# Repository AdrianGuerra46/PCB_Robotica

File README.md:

# PCB Robótica Industrial

Este proyecto fue realizado para compactar y profesionalizar el apartado electrónico del proyecto final de la asignatura Robótica industrial (materia de pregrado de ingeniería mecatrónica en la Universidad EIA) el cual fue construir un Robot Scara. 

Esta PCB debia generar conexión entre los siguientes componentes: 

- Raspberry Pi Pico
- Driver Dual motor TB6612FNG
- Servo Motor "Micro Servo 9g"
- Dos motores DC 12V - 200RPM con Encoder
- 4 Finales de Carrera

La PCB fue diseñada y exportada desde el software Kicad7.

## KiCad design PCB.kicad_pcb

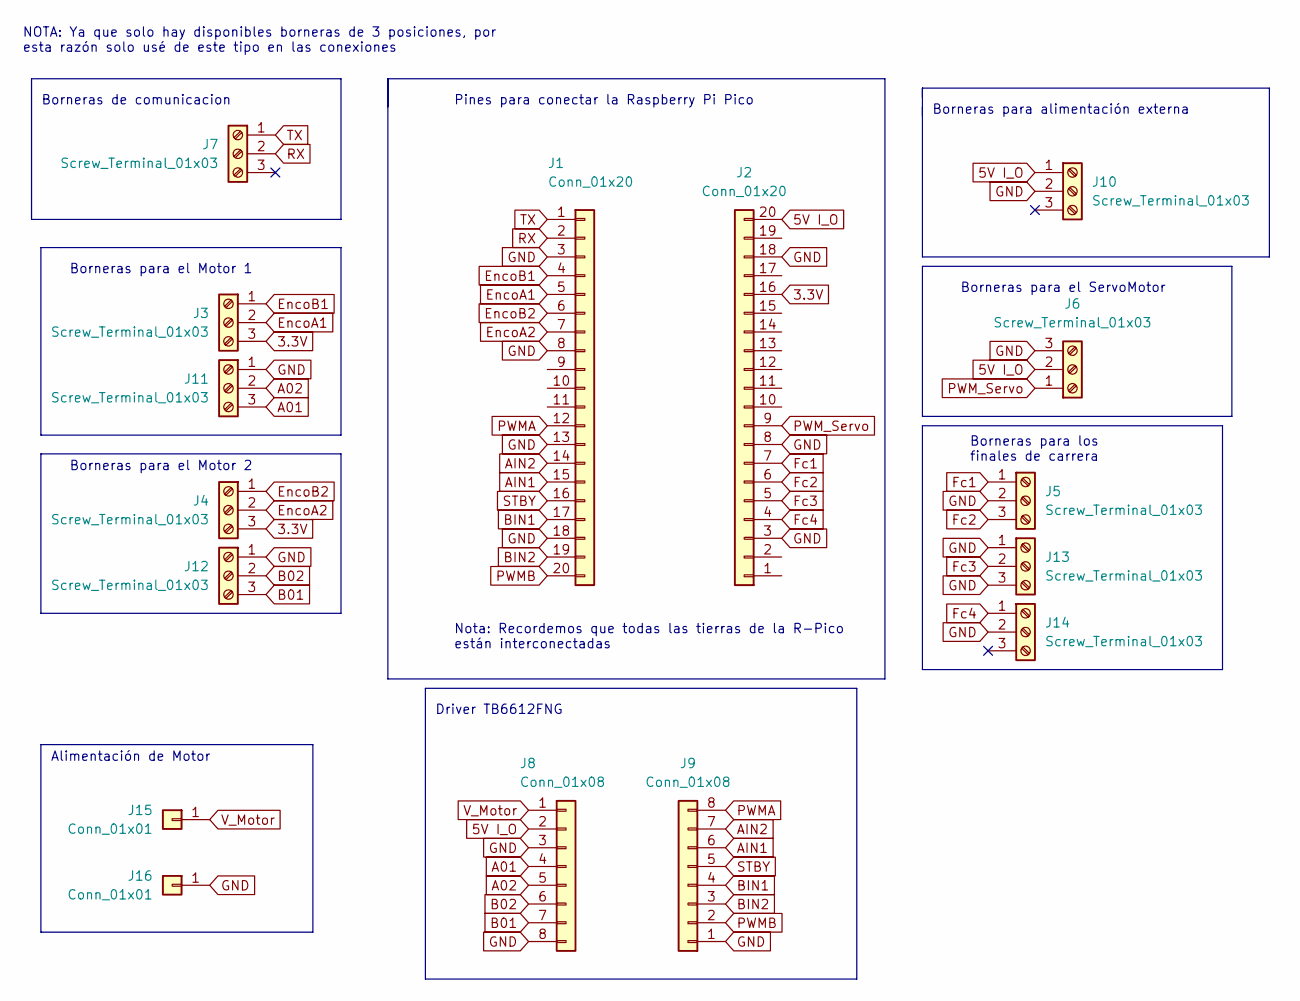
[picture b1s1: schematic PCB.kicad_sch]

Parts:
J1, J2: Conn_01x20; PinSocket_1x20_P2.54mm_Vertical
J3, J4, J5, J6, J7, J10, J11, J12, J13, J14: Screw_Terminal_01x03; PhoenixContact_MSTBVA_2,5_3-G_1x03_P5.00mm_Vertical
J8, J9: Conn_01x08; PinSocket_1x08_P2.54mm_Vertical
J15, J16: Conn_01x01; PinHeader_1x01_P2.54mm_Vertical

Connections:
3.3V: J2.16, J3.3, J4.3
5V I_O: J2.20, J6.2, J8.2, J10.1
A01: J8.4, J11.3
A02: J8.5, J11.2
AIN1: J1.15, J9.6
AIN2: J1.14, J9.7
B01: J8.7, J12.3
B02: J8.6, J12.2
BIN1: J1.17, J9.4
BIN2: J1.19, J9.3
EncoA1: J1.5, J3.2
EncoA2: J1.7, J4.2
EncoB1: J1.4, J3.1
EncoB2: J1.6, J4.1
Fc1: J2.7, J5.1
Fc2: J2.6, J5.3
Fc3: J2.5, J13.2
Fc4: J2.4, J14.1
GND: J1.3, J1.8, J1.13, J1.18, J2.3, J2.8, J2.18, J5.2, J6.3, J8.3, J8.8, J9.1, J10.2, J11.1, J12.1, J13.1, J13.3, J14.2, J16.1
PWMA: J1.12, J9.8
PWMB: J1.20, J9.2
PWM_Servo: J2.9, J6.1
RX: J1.2, J7.2
STBY: J1.16, J9.5
TX: J1.1, J7.1
V_Motor: J8.1, J15.1

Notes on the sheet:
Nota: Recordemos que todas las tierras de la R-Pico están interconectadas
Alimentación de Motor
Borneras para el ServoMotor
Borneras de comunicacion
Borneras para el Motor 1
Driver TB6612FNG
Pines para conectar la Raspberry Pi Pico
Borneras para el Motor 2
Borneras para los finales de carrera
Borneras para alimentación externa
NOTA: Ya que solo hay disponibles borneras de 3 posiciones, por esta razón solo usé de este tipo en las conexiones

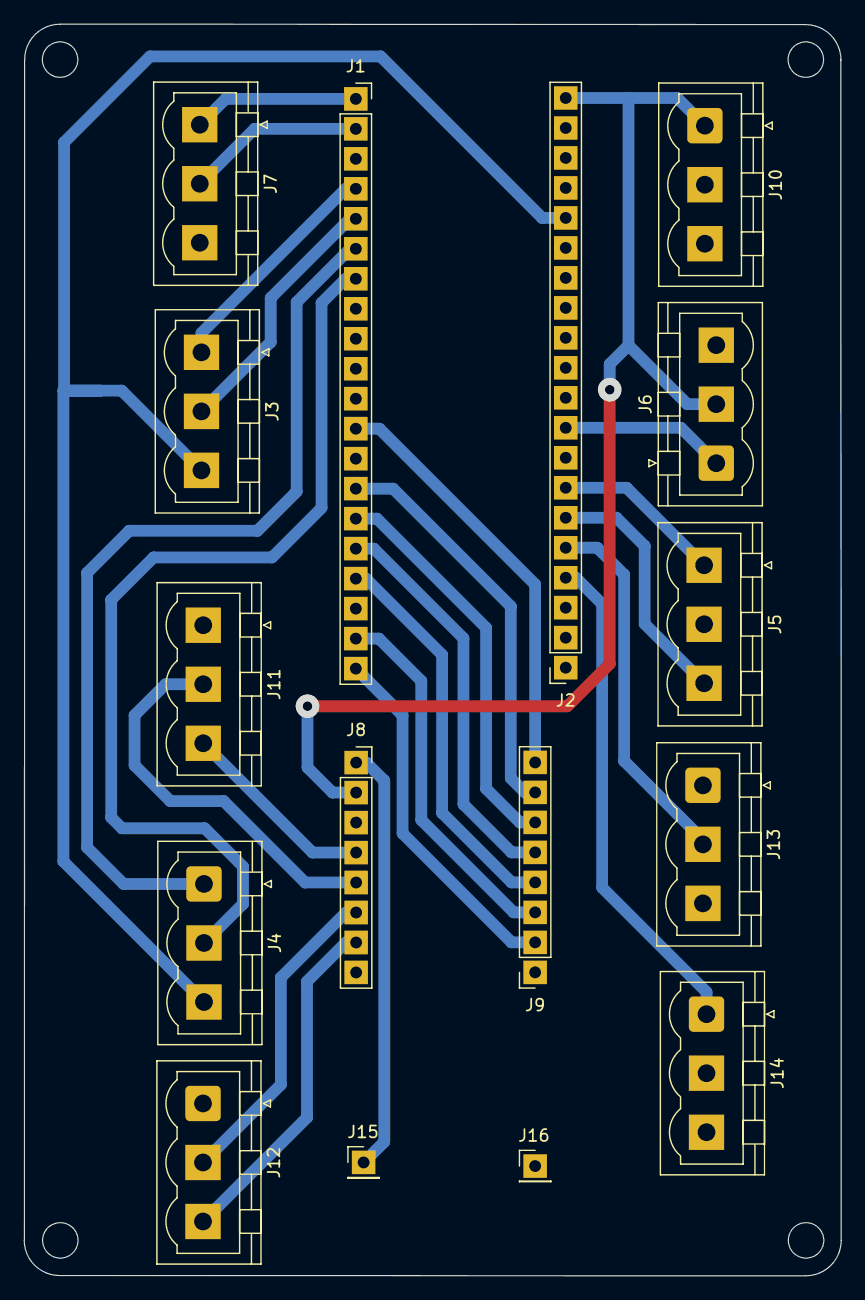
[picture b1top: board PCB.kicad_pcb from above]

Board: 2 copper layers, 69.2 x 106.0 mm, 16 parts (0 on the bottom side), 26 nets.

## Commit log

2024-01-06 Agrego el proyecto completo
2024-06-07 07-06-2024
2024-09-06 06/09/2024
2025-07-20 Formateo 20/07
